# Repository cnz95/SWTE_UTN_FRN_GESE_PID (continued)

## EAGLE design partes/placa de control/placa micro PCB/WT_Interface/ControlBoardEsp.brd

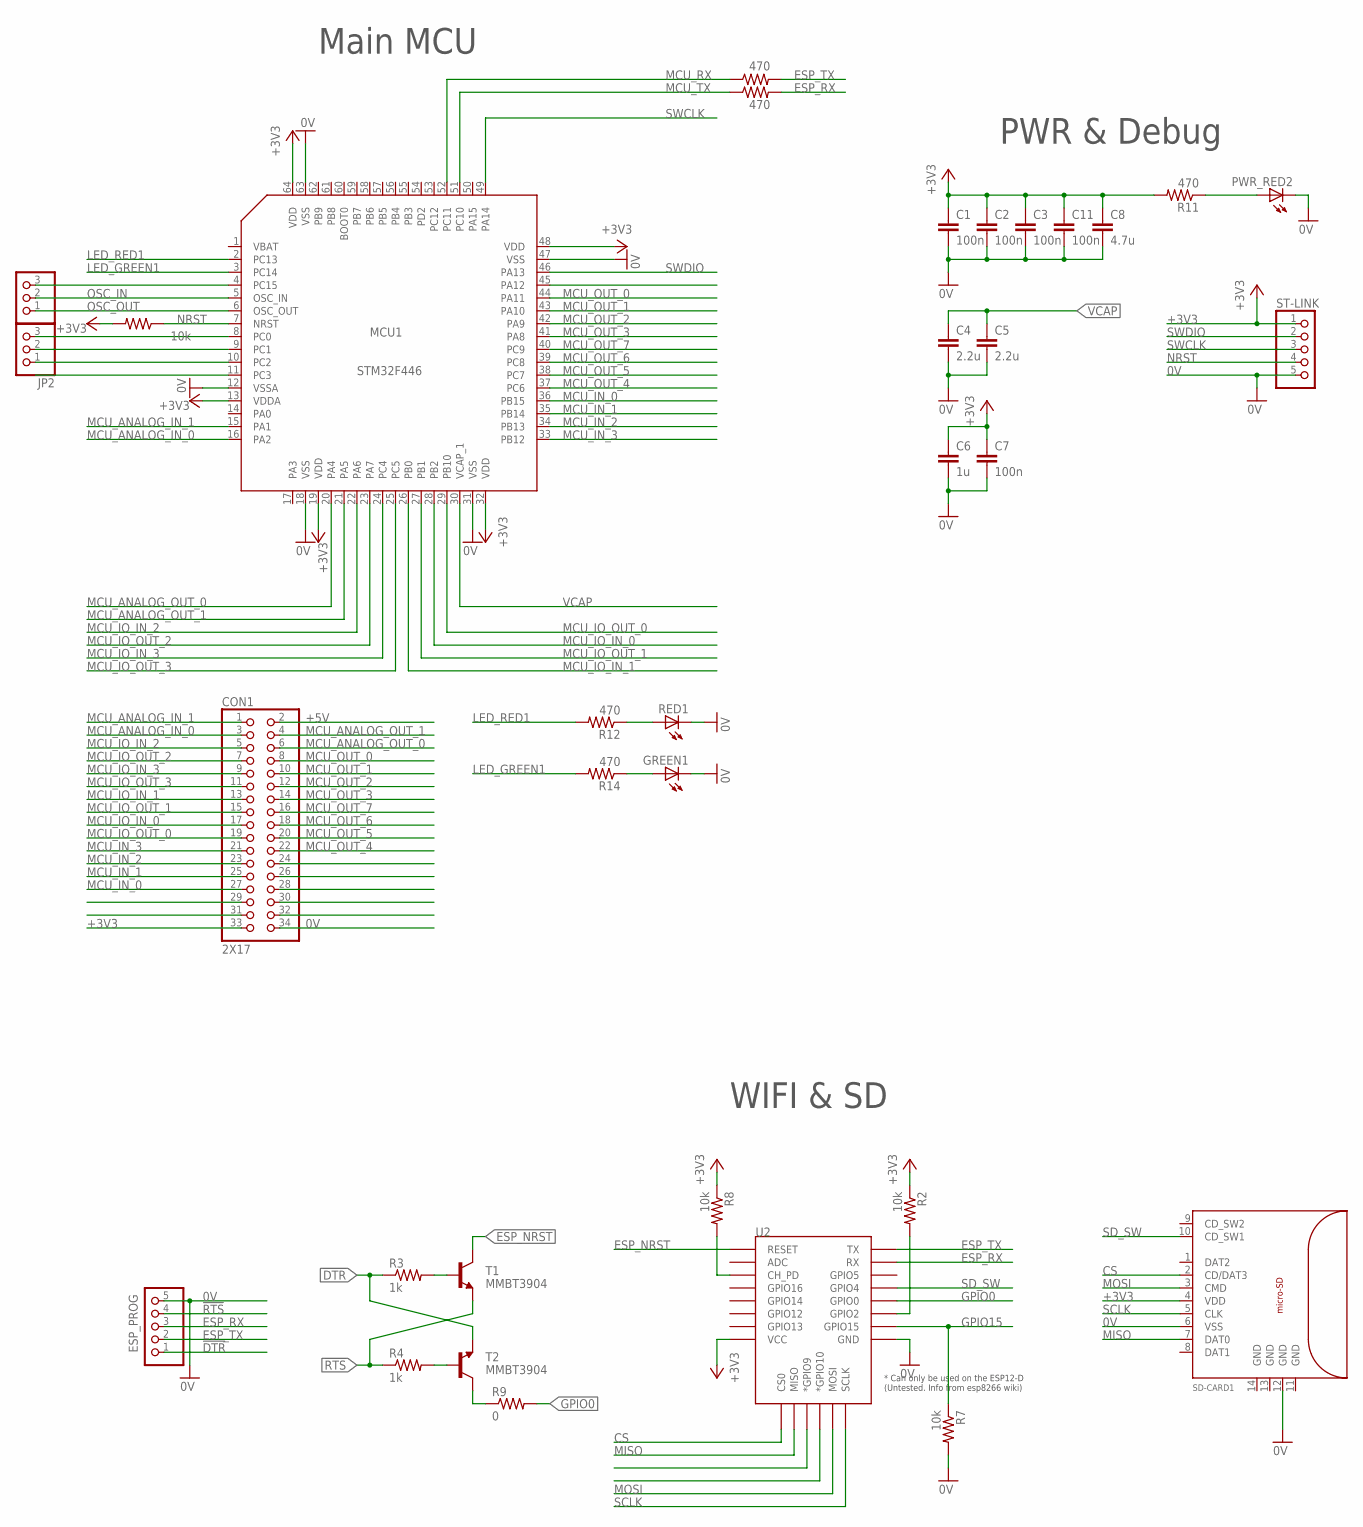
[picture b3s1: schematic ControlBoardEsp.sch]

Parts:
C1, C2, C3, C7, C11: 100n; C0402
C4, C5: 2.2u; C0402
C6: 1u; C0402
C8: 4.7u; C0402
CON1: 2X17
ESP_PROG: PINHD-1X5; 1X05
GREEN1: LEDCHIP-LED0805; CHIP-LED0805
JP1, JP2: PINHD-1X3; 1X03
MCU1: STM32F446; LQFP-64
PWR_RED2: LEDCHIP-LED0805; CHIP-LED0805
R1, R2, R7, R8: 10k; R0402
R3: 1k; R0402
R4: 1k; R1206
R5, R6, R11, R12, R14: 470; R0402
R9: 0; R1206
RED1: LEDCHIP-LED0805; CHIP-LED0805
SD-CARD1: MICRO-SD; MICRO_SD_FOOTPRINT
ST-LINK: PINHD-1X5; 1X05
T1, T2: MMBT3904; SOT23-BEC
U2: ESP12ESMD; ESP12E-SMD

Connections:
0V: C1.2, C2.2, C3.2, C4.2, C5.2, C6.2, C7.2, C8.2, C11.2, CON1.34, ESP_PROG.5, GREEN1.C, MCU1.12 (VSSA), MCU1.18 (VSS), MCU1.31 (VSS), MCU1.47 (VSS), MCU1.63 (VSS), PWR_RED2.C, R7.2, RED1.C, SD-CARD1.6 (VSS), SD-CARD1.12 (GND), ST-LINK.5, U2.GND
!DTR!: ESP_PROG.1, R3.1, T2.E
!RTS!: ESP_PROG.4, R4.1, T1.E
+3V3: C1.1, C2.1, C3.1, C6.1, C7.1, C8.1, C11.1, CON1.33, MCU1.13 (VDDA), MCU1.19 (VDD), MCU1.32 (VDD), MCU1.48 (VDD), MCU1.64 (VDD), R1.2, R2.1, R8.1, R11.2, SD-CARD1.4 (VDD), ST-LINK.1, U2.VCC
+5V: CON1.2
CS: SD-CARD1.2 (CD/DAT3), U2.CS0
ESP_NRST: T1.C, U2.RESET
ESP_RX: ESP_PROG.3, R6.2, U2.RXD0 (RX)
ESP_TX: ESP_PROG.2, R5.2, U2.TXD0 (TX)
GPIO0: R9.2, U2.GPIO0
GPIO15: R7.1, U2.GPIO15
LED_GREEN1: MCU1.3 (PC14), R14.2
LED_RED1: MCU1.2 (PC13), R12.2
MCU_ANALOG_IN_0: CON1.3, MCU1.16 (PA2)
MCU_ANALOG_IN_1: CON1.1, MCU1.15 (PA1)
MCU_ANALOG_OUT_0: CON1.6, MCU1.20 (PA4)
MCU_ANALOG_OUT_1: CON1.4, MCU1.21 (PA5)
MCU_IN_0: CON1.27, MCU1.36 (PB15)
MCU_IN_1: CON1.25, MCU1.35 (PB14)
MCU_IN_2: CON1.23, MCU1.34 (PB13)
MCU_IN_3: CON1.21, MCU1.33 (PB12)
MCU_IO_IN_0: CON1.17, MCU1.28 (PB2)
MCU_IO_IN_1: CON1.13, MCU1.26 (PB0)
MCU_IO_IN_2: CON1.5, MCU1.22 (PA6)
MCU_IO_IN_3: CON1.9, MCU1.24 (PC4)
MCU_IO_OUT_0: CON1.19, MCU1.29 (PB10)
MCU_IO_OUT_1: CON1.15, MCU1.27 (PB1)
MCU_IO_OUT_2: CON1.7, MCU1.23 (PA7)
MCU_IO_OUT_3: CON1.11, MCU1.25 (PC5)
MCU_OUT_0: CON1.8, MCU1.44 (PA11)
MCU_OUT_1: CON1.10, MCU1.43 (PA10)
MCU_OUT_2: CON1.12, MCU1.42 (PA9)
MCU_OUT_3: CON1.14, MCU1.41 (PA8)
MCU_OUT_4: CON1.22, MCU1.37 (PC6)
MCU_OUT_5: CON1.20, MCU1.38 (PC7)
MCU_OUT_6: CON1.18, MCU1.39 (PC8)
MCU_OUT_7: CON1.16, MCU1.40 (PC9)
MCU_RX: MCU1.52 (PC11), R5.1
MCU_TX: MCU1.51 (PC10), R6.1
MISO: SD-CARD1.7 (DAT0), U2.MISO
MOSI: SD-CARD1.3 (CMD), U2.MOSI
unnamed: R2.2, U2.GPIO2
unnamed: R3.2, T1.B
unnamed: R4.2, T2.B
unnamed: R8.2, U2.CH_PD
unnamed: R9.1, T2.C
unnamed: PWR_RED2.A, R11.1
unnamed: R12.1, RED1.A
unnamed: JP2.1, MCU1.10 (PC2)
unnamed: GREEN1.A, R14.1
unnamed: JP2.2, MCU1.9 (PC1)
unnamed: JP2.3, MCU1.8 (PC0)
unnamed: JP1.3, MCU1.4 (PC15)
NRST: MCU1.7 (NRST), R1.1, ST-LINK.4
OSC_IN: JP1.2, MCU1.5 (OSC_IN)
OSC_OUT: JP1.1, MCU1.6 (OSC_OUT)
SCLK: SD-CARD1.5 (CLK), U2.SCLK
SD_SW: SD-CARD1.10 (CD_SW1), U2.GPIO4
SWCLK: MCU1.49 (PA14), ST-LINK.3
SWDIO: MCU1.46 (PA13), ST-LINK.2
VCAP: C4.1, C5.1, MCU1.30 (VCAP_1)

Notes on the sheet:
PWR & Debug
Main MCU
WIFI & SD

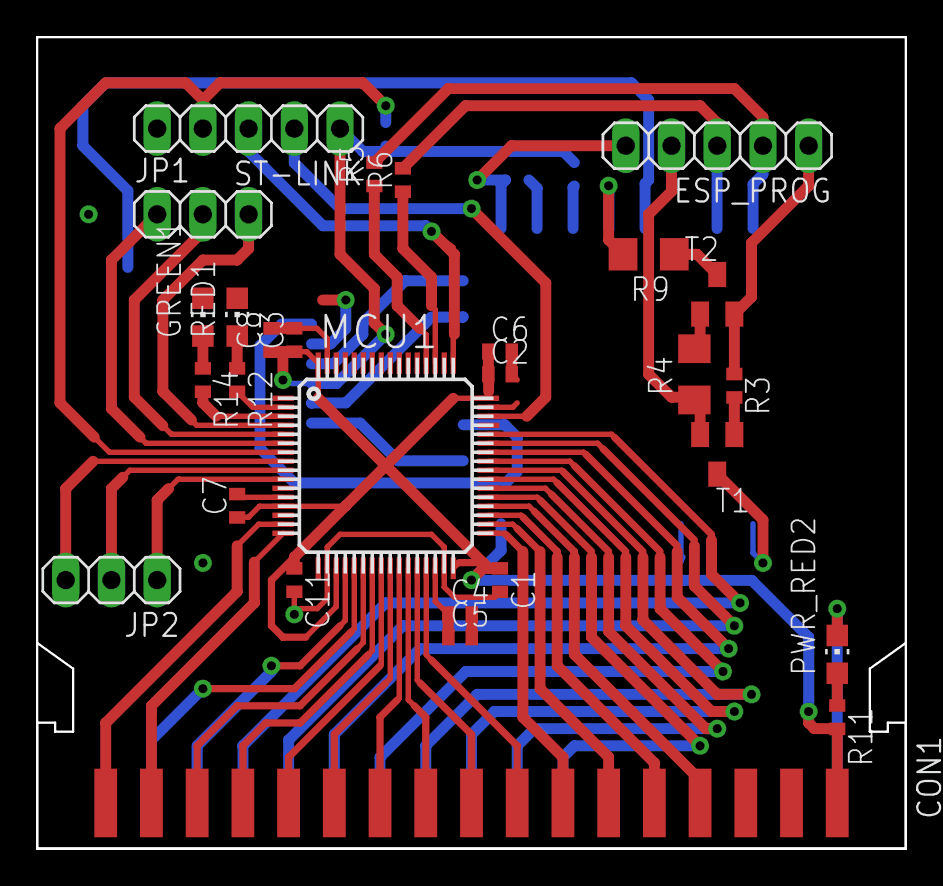
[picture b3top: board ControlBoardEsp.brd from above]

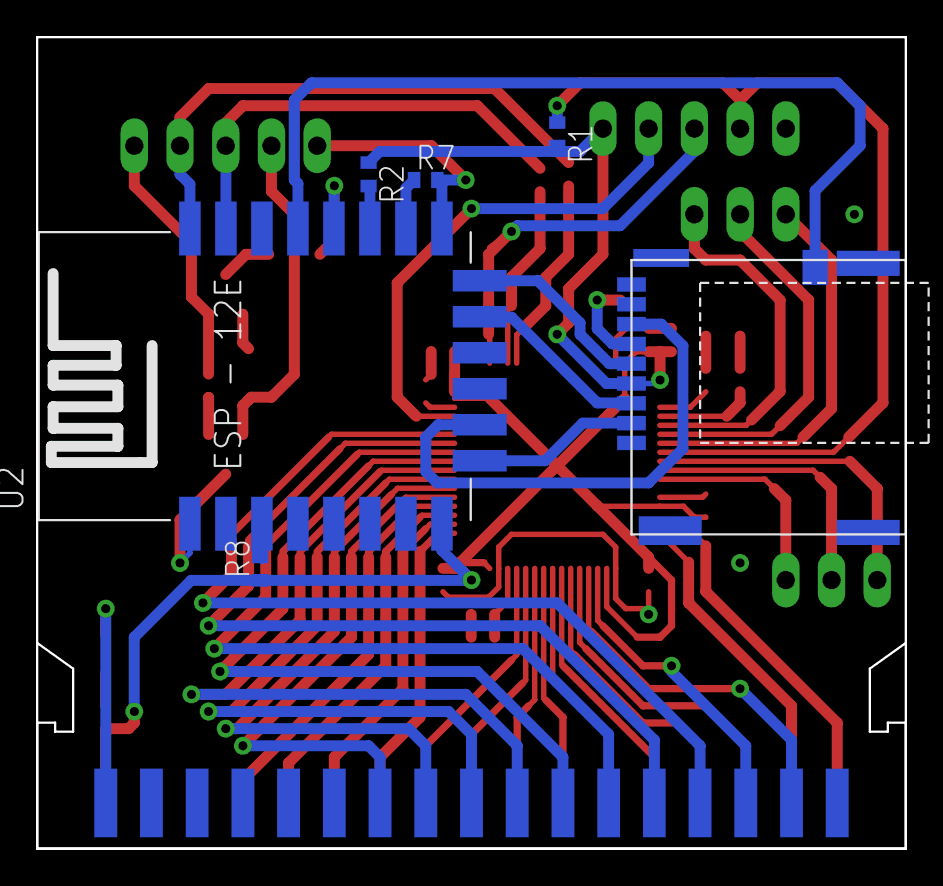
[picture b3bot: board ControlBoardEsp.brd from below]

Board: 2 copper layers, 48.3 x 45.1 mm, 34 parts (6 on the bottom side), 60 nets.

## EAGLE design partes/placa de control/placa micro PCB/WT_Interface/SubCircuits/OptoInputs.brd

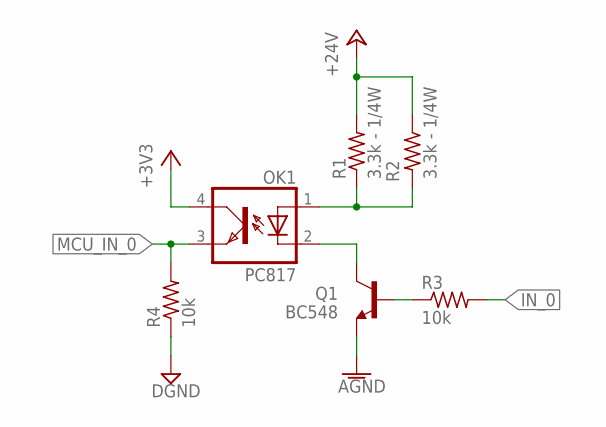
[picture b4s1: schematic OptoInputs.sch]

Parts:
OK1: PC817; DIL04
Q1: BC548; TO92-EBC
R1, R2: 3.3k - 1/4W; 0204V
R3: 10k; 0204/5
R4: 10k; R0402

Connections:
+3V3: OK1.4 (COL)
+24V: R1.2, R2.1
AGND: Q1.E
DGND: R4.1
IN_0: R3.2
MCU_IN_0: OK1.3 (EMIT), R4.2
unnamed: OK1.1 (A), R1.1, R2.2
unnamed: OK1.2 (C), Q1.C
unnamed: Q1.B, R3.1

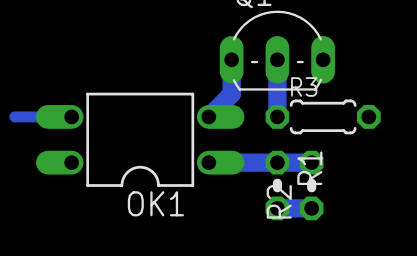
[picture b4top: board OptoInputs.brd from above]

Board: 2 copper layers, 6 parts (1 on the bottom side), 5 nets.

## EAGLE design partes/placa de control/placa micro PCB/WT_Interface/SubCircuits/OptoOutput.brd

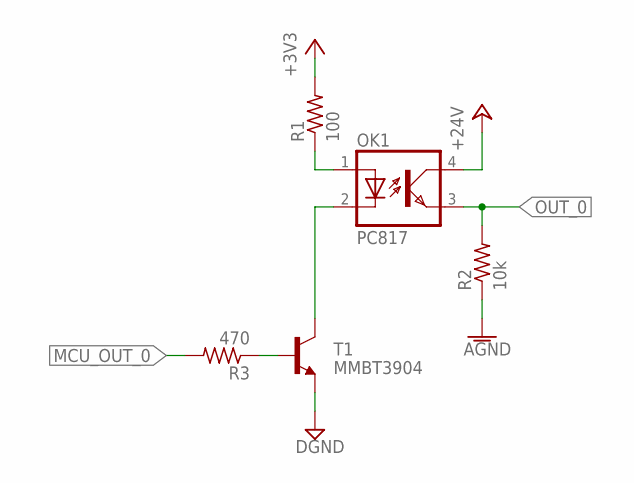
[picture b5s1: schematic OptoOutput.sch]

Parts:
OK1: PC817; DIL04
R1: 100; R0402
R2: 10k; R0402
R3: 470; 0204/5
T1: MMBT3904; SOT23-BEC

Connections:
+3V3: R1.2
+24V: OK1.4 (COL)
AGND: R2.1
DGND: T1.E
MCU_OUT_0: R3.2
unnamed: OK1.2 (C), T1.C
unnamed: R3.1, T1.B
unnamed: OK1.1 (A), R1.1
OUT_0: OK1.3 (EMIT), R2.2

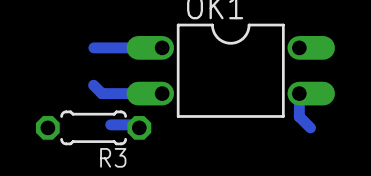
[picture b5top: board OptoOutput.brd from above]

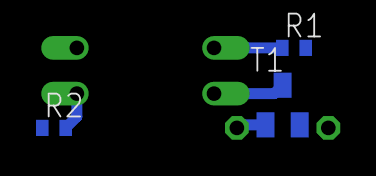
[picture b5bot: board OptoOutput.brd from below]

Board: 2 copper layers, 5 parts (3 on the bottom side), 4 nets.

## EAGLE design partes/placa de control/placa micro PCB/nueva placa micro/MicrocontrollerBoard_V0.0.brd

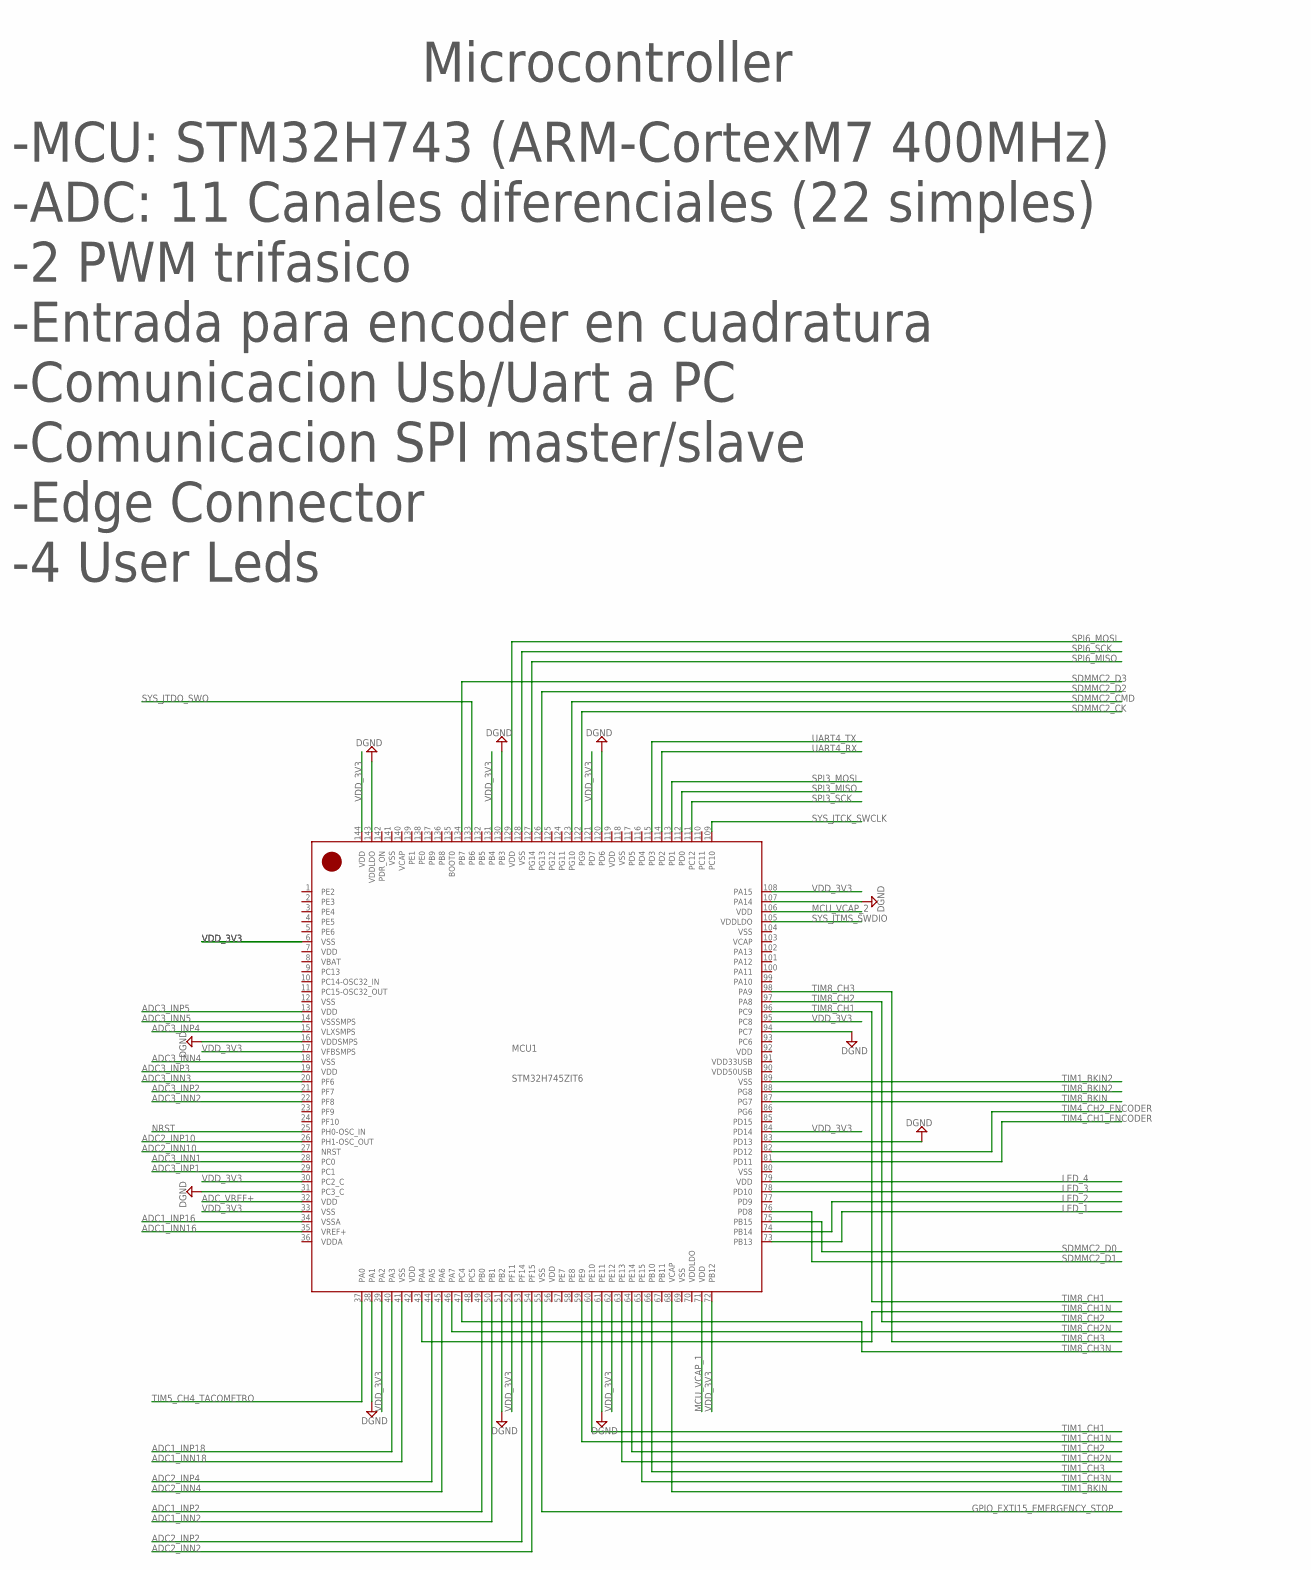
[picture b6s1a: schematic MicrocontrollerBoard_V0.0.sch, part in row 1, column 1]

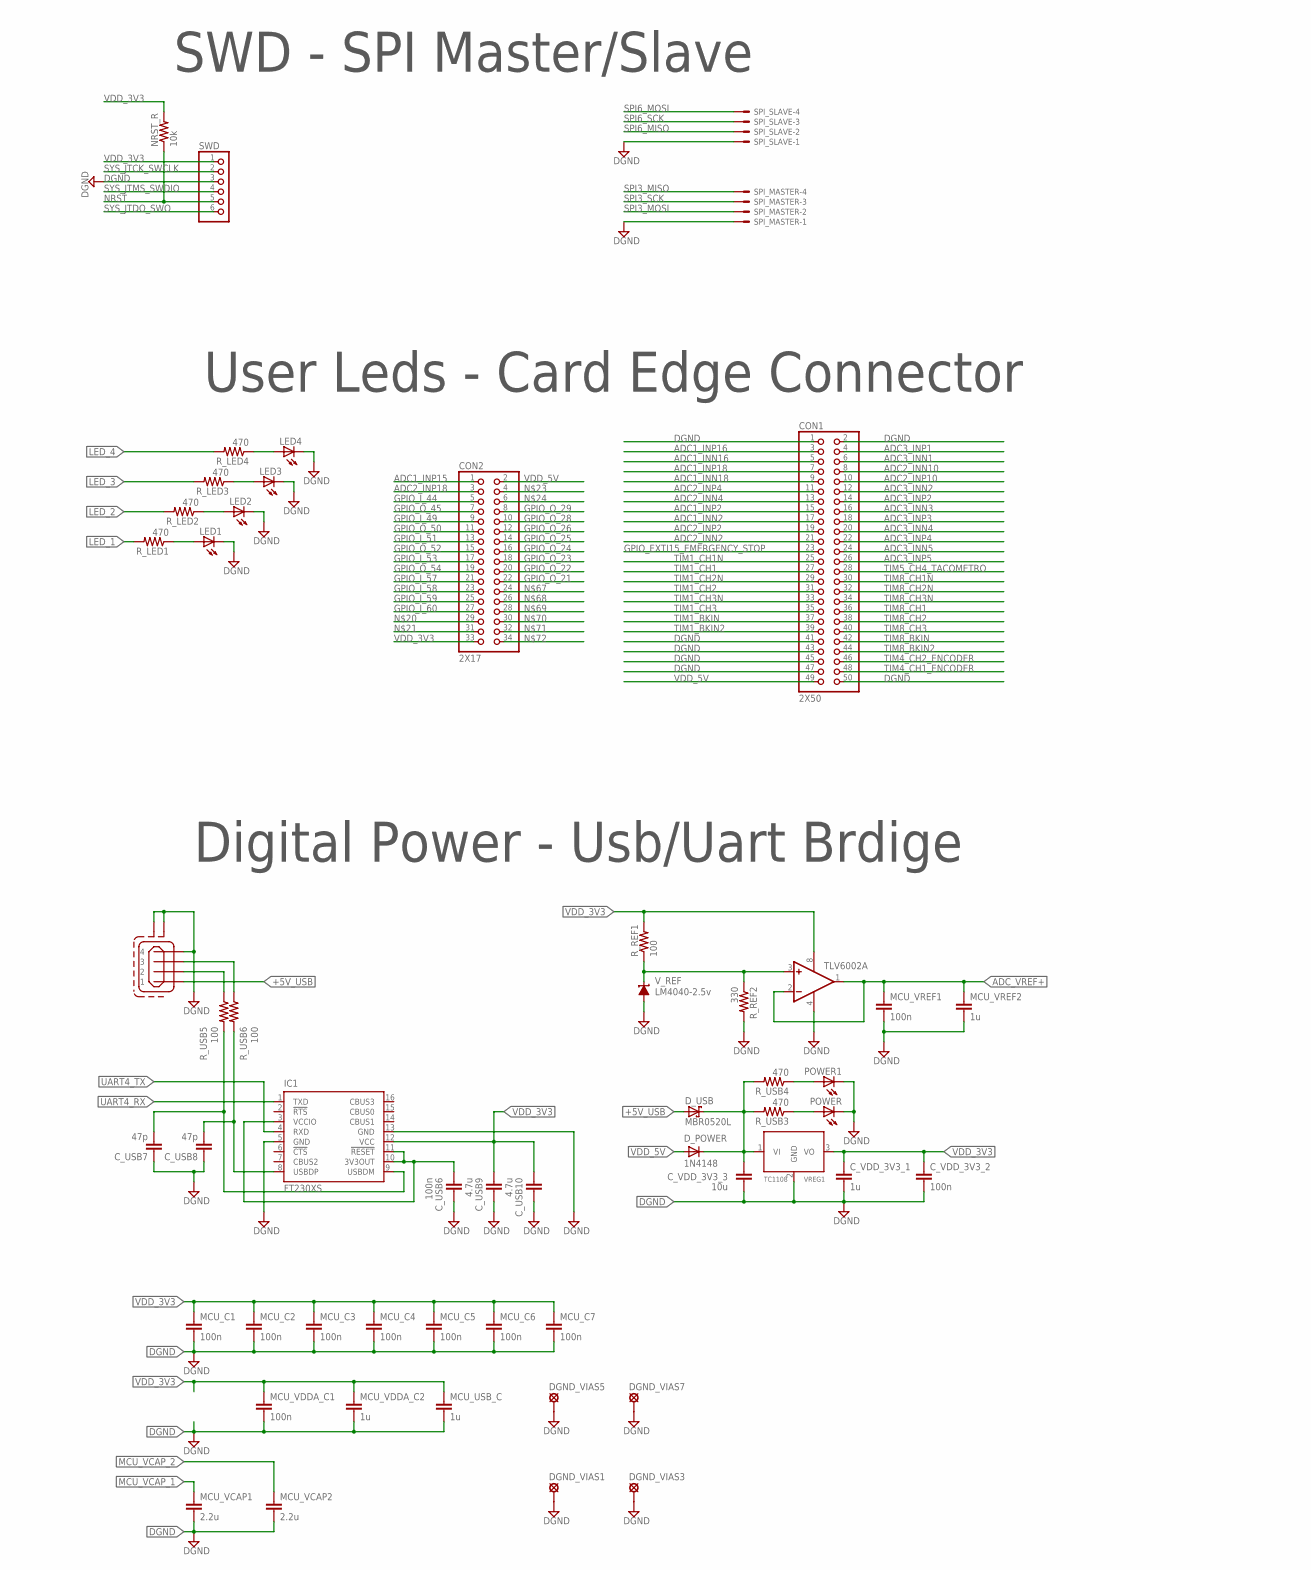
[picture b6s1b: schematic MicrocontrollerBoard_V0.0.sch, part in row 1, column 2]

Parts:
CON1: 2X50; 2X25
CON2: 2X17
C_USB6: 100n; C0402
C_USB7, C_USB8: 47p; C0402
C_USB9, C_USB10: 4.7u; C0402
C_VDD_3V3_1: 1u; C0603K
C_VDD_3V3_2: 100n; C0603K
C_VDD_3V3_3: 10u; C0603K
DGND_VIAS1, DGND_VIAS3, DGND_VIAS5, DGND_VIAS7: LSP10
D_POWER: 1N4148; SMA-DO214AC
D_USB: MBR0520L; SOD-123
IC1: FT230XS; SSOP16
LED1, LED2, LED3, LED4: LEDCHIPLED_0805; CHIPLED_0805
MCU1: STM32H745ZIT6144; LQFP144
MCU_C1, MCU_C2, MCU_C3, MCU_C4, MCU_C5, MCU_C6, MCU_C7: 100n; C0402
MCU_USB_C: 1u; C0402
MCU_VCAP1, MCU_VCAP2: 2.2u; C0402
MCU_VDDA_C1: 100n; C0402
MCU_VDDA_C2: 1u; C0402
MCU_VREF1: 100n; C0402
MCU_VREF2: 1u; C0402
NRST_R: 10k; R0402
POWER, POWER1: LEDCHIPLED_0805; CHIPLED_0805
R_LED1, R_LED2, R_LED3, R_LED4: 470; R0402
R_REF1: 100; R0805
R_REF2: 330; R0805
R_USB3, R_USB4: 470; R0402
R_USB5, R_USB6: 100; R0402
SPI_MASTER: 22-23-2041
SPI_SLAVE: 22-23-2041
SWD: PINHD-1X6/90; 1X06/90
TLV6002: TL082D; SO08
VREG1: TC1108'SOT-223'; SOT-223
V_REF: LM4040-2.5v; DBZ_R-PDSO-G3
X2: MINI-USB_SHIELD4P-85-32004-00X; 85-32004-00X

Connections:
+5V_USB: D_USB.A (IN), X2.1
ADC1_INN2: CON1.17, MCU1.50 (PB1)
ADC1_INN16: CON1.5, MCU1.35 (VREF+)
ADC1_INN18: CON1.9, MCU1.41 (VSS)
ADC1_INP2: CON1.15, MCU1.49 (PB0)
ADC1_INP15: CON2.1
ADC1_INP16: CON1.3, MCU1.34 (VSSA)
ADC1_INP18: CON1.7, MCU1.40 (PA3)
ADC2_INN2: CON1.21, MCU1.54 (PF15)
ADC2_INN4: CON1.13, MCU1.45 (PA6)
ADC2_INN10: CON1.8, MCU1.27 (NRST)
ADC2_INP2: CON1.19, MCU1.53 (PF14)
ADC2_INP4: CON1.11, MCU1.44 (PA5)
ADC2_INP10: CON1.10, MCU1.26 (PH1-OSC_OUT)
ADC2_INP18: CON2.3
ADC3_INN1: CON1.6, MCU1.28 (PC0)
ADC3_INN2: CON1.12, MCU1.22 (PF8)
ADC3_INN3: CON1.16, MCU1.20 (PF6)
ADC3_INN4: CON1.20, MCU1.18 (VSS)
ADC3_INN5: CON1.24, MCU1.14 (VSSSMPS)
ADC3_INP1: CON1.4, MCU1.29 (PC1)
ADC3_INP2: CON1.14, MCU1.21 (PF7)
ADC3_INP3: CON1.18, MCU1.19 (VDD)
ADC3_INP4: CON1.22, MCU1.15 (VLXSMPS)
ADC3_INP5: CON1.26, MCU1.13 (VDD)
ADC_VREF+: MCU1.32 (VDD), MCU_VREF1.1, MCU_VREF2.1, TLV6002.1 (OUT), TLV6002.2 (-IN)
DGND: CON1.1, CON1.2, CON1.41, CON1.43, CON1.45, CON1.47, CON1.50, C_USB6.1, C_USB7.1, C_USB8.1, C_USB9.1, C_USB10.1, C_VDD_3V3_1.2, C_VDD_3V3_2.2, C_VDD_3V3_3.2, DGND_VIAS1.MP, DGND_VIAS3.MP, DGND_VIAS5.MP, DGND_VIAS7.MP, IC1.5 (GND), IC1.13 (GND), LED1.C, LED2.C, LED3.C, LED4.C, MCU1.16 (VDDSMPS), MCU1.31 (PC3_C), MCU1.38 (PA1), MCU1.51 (PB2), MCU1.61 (PE11), MCU1.83 (PD13), MCU1.94 (PC7), MCU1.107 (PA14), MCU1.120 (PD6), MCU1.130 (PB3), MCU1.143 (VDDLDO), MCU_C1.2, MCU_C2.2, MCU_C3.2, MCU_C4.2, MCU_C5.2, MCU_C6.2, MCU_C7.2, MCU_USB_C.2, MCU_VCAP1.2, MCU_VCAP2.2, MCU_VDDA_C1.2, MCU_VDDA_C2.2, MCU_VREF1.2, MCU_VREF2.2, POWER.C, POWER1.C, R_REF2.2, SPI_MASTER.1, SPI_SLAVE.1, SWD.3, TLV6002.4 (V-), VREG1.2 (GND), V_REF.2 (A), X2.4, X2.M1 (S1), X2.M2 (S2)
GPIO_EXTI15_EMERGENCY_STOP: CON1.23, MCU1.55 (VSS)
GPIO_I_44: CON2.5
GPIO_I_49: CON2.9
GPIO_I_51: CON2.13
GPIO_I_53: CON2.17
GPIO_I_57: CON2.21
GPIO_I_58: CON2.23
GPIO_I_59: CON2.25
GPIO_I_60: CON2.27
GPIO_O_21: CON2.22
GPIO_O_22: CON2.20
GPIO_O_23: CON2.18
GPIO_O_24: CON2.16
GPIO_O_25: CON2.14
GPIO_O_26: CON2.12
GPIO_O_28: CON2.10
GPIO_O_29: CON2.8
GPIO_O_45: CON2.7
GPIO_O_50: CON2.11
GPIO_O_52: CON2.15
GPIO_O_54: CON2.19
LED_1: MCU1.73 (PB13), R_LED1.2
LED_2: MCU1.74 (PB14), R_LED2.2
LED_3: MCU1.78 (PD10), R_LED3.2
LED_4: MCU1.79 (VDD), R_LED4.2
MCU_VCAP_1: MCU1.71 (VDD), MCU_VCAP1.1
MCU_VCAP_2: MCU1.106 (VDD), MCU_VCAP2.1
unnamed: LED4.A, R_LED4.1
unnamed: POWER1.A, R_USB4.1
unnamed: LED3.A, R_LED3.1
unnamed: C_USB6.2, IC1.3 (VCCIO), IC1.10 (3V3OUT), IC1.11 (!RESET)
unnamed: C_VDD_3V3_3.1, D_POWER.K (C), D_USB.C (OUT), R_USB3.2, R_USB4.2, VREG1.1 (VI)
unnamed: C_USB8.2, IC1.8 (USBDP), R_USB6.2
unnamed: C_USB7.2, IC1.9 (USBDM), R_USB5.2
unnamed: R_USB5.1, X2.2
unnamed: R_USB6.1, X2.3
unnamed: POWER.A, R_USB3.1
unnamed: R_REF1.1, R_REF2.1, TLV6002.3 (+IN), V_REF.1 (C)
unnamed: LED1.A, R_LED1.1
unnamed: LED2.A, R_LED2.1
NRST: MCU1.25 (PH0-OSC_IN), NRST_R.1, SWD.5
SDMMC2_CK: MCU1.122 (PG9)
SDMMC2_CMD: MCU1.123 (PG10)
SDMMC2_D0: MCU1.75 (PB15)
SDMMC2_D1: MCU1.76 (PD8)
SDMMC2_D2: MCU1.126 (PG13)
SDMMC2_D3: MCU1.134 (PB7)
SPI3_MISO: MCU1.112 (PD0), SPI_MASTER.4
SPI3_MOSI: MCU1.113 (PD1), SPI_MASTER.2
SPI3_SCK: MCU1.111 (PC12), SPI_MASTER.3
SPI6_MISO: MCU1.127 (PG14), SPI_SLAVE.2
SPI6_MOSI: MCU1.129 (VDD), SPI_SLAVE.4
SPI6_SCK: MCU1.128 (VSS), SPI_SLAVE.3
SYS_JTCK_SWCLK: MCU1.109 (PC10), SWD.2
SYS_JTDO_SWO: MCU1.133 (PB6), SWD.6
SYS_JTMS_SWDIO: MCU1.105 (VDDLDO), SWD.4
TIM1_BKIN: CON1.37, MCU1.68 (VCAP)
TIM1_BKIN2: CON1.39, MCU1.89 (VSS)
TIM1_CH1: CON1.27, MCU1.60 (PE10)
TIM1_CH1N: CON1.25, MCU1.59 (PE9)
TIM1_CH2: CON1.31, MCU1.64 (PE14)
TIM1_CH2N: CON1.29, MCU1.63 (PE13)
TIM1_CH3: CON1.35, MCU1.66 (PB10)
TIM1_CH3N: CON1.33, MCU1.65 (PE15)
TIM4_CH1_ENCODER: CON1.48, MCU1.81 (PD11)
TIM4_CH2_ENCODER: CON1.46, MCU1.82 (PD12)
TIM5_CH4_TACOMETRO: CON1.28, MCU1.37 (PA0)
TIM8_BKIN: CON1.42, MCU1.87 (PG7)
TIM8_BKIN2: CON1.44, MCU1.88 (PG8)
TIM8_CH1: CON1.36, MCU1.96 (PC9)
TIM8_CH1N: CON1.30, MCU1.43 (PA4)
TIM8_CH2: CON1.38, MCU1.97 (PA8)
TIM8_CH2N: CON1.32, MCU1.46 (PA7)
TIM8_CH3: CON1.40, MCU1.98 (PA9)
TIM8_CH3N: CON1.34, MCU1.47 (PC4)
UART4_RX: IC1.1 (TXD), MCU1.114 (PD2)
UART4_TX: IC1.4 (RXD), MCU1.115 (PD3)
VDD_3V3: CON2.33, C_USB9.2, C_USB10.2, C_VDD_3V3_1.1, C_VDD_3V3_2.1, IC1.12 (VCC), MCU1.6 (VSS), MCU1.17 (VFBSMPS), MCU1.30 (PC2_C), MCU1.33 (VSS), MCU1.39 (PA2), MCU1.52 (PF11), MCU1.62 (PE12), MCU1.72 (PB12), MCU1.84 (PD14), MCU1.95 (PC8), MCU1.108 (PA15), MCU1.121 (PD7), MCU1.131 (PB4), MCU1.144 (VDD), MCU_C1.1, MCU_C2.1, MCU_C3.1, MCU_C4.1, MCU_C5.1, MCU_C6.1, MCU_C7.1, MCU_USB_C.1, MCU_VDDA_C1.1, MCU_VDDA_C2.1, NRST_R.2, R_REF1.2, SWD.1, TLV6002.8 (V+), VREG1.3 (VO)
VDD_5V: CON1.49, CON2.2, D_POWER.A

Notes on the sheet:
Microcontroller
SWD - SPI Master/Slave
User Leds - Card Edge Connector
Digital Power - Usb/Uart Brdige
-MCU: STM32H743 (ARM-CortexM7 400MHz) -ADC: 11 Canales diferenciales (22 simples) -2 PWM trifasico -Entrada para encoder en cuadratura -Comunicacion Usb/Uart a PC -Comunicacion SPI master/slave -Edge Connector -4 User Leds

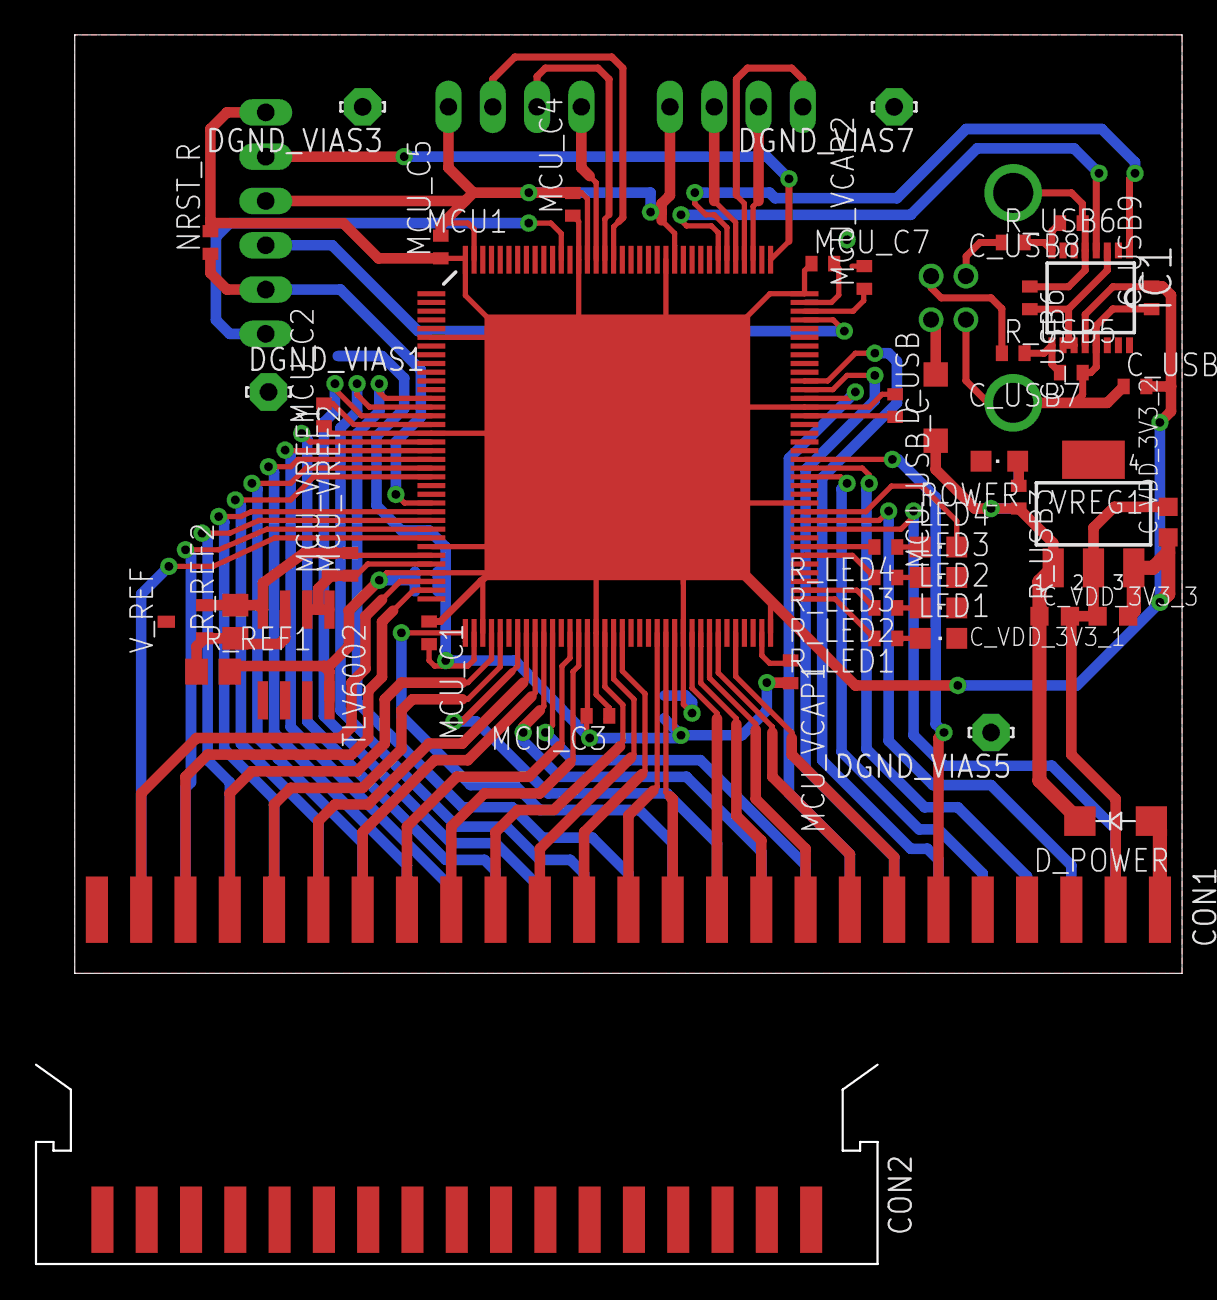
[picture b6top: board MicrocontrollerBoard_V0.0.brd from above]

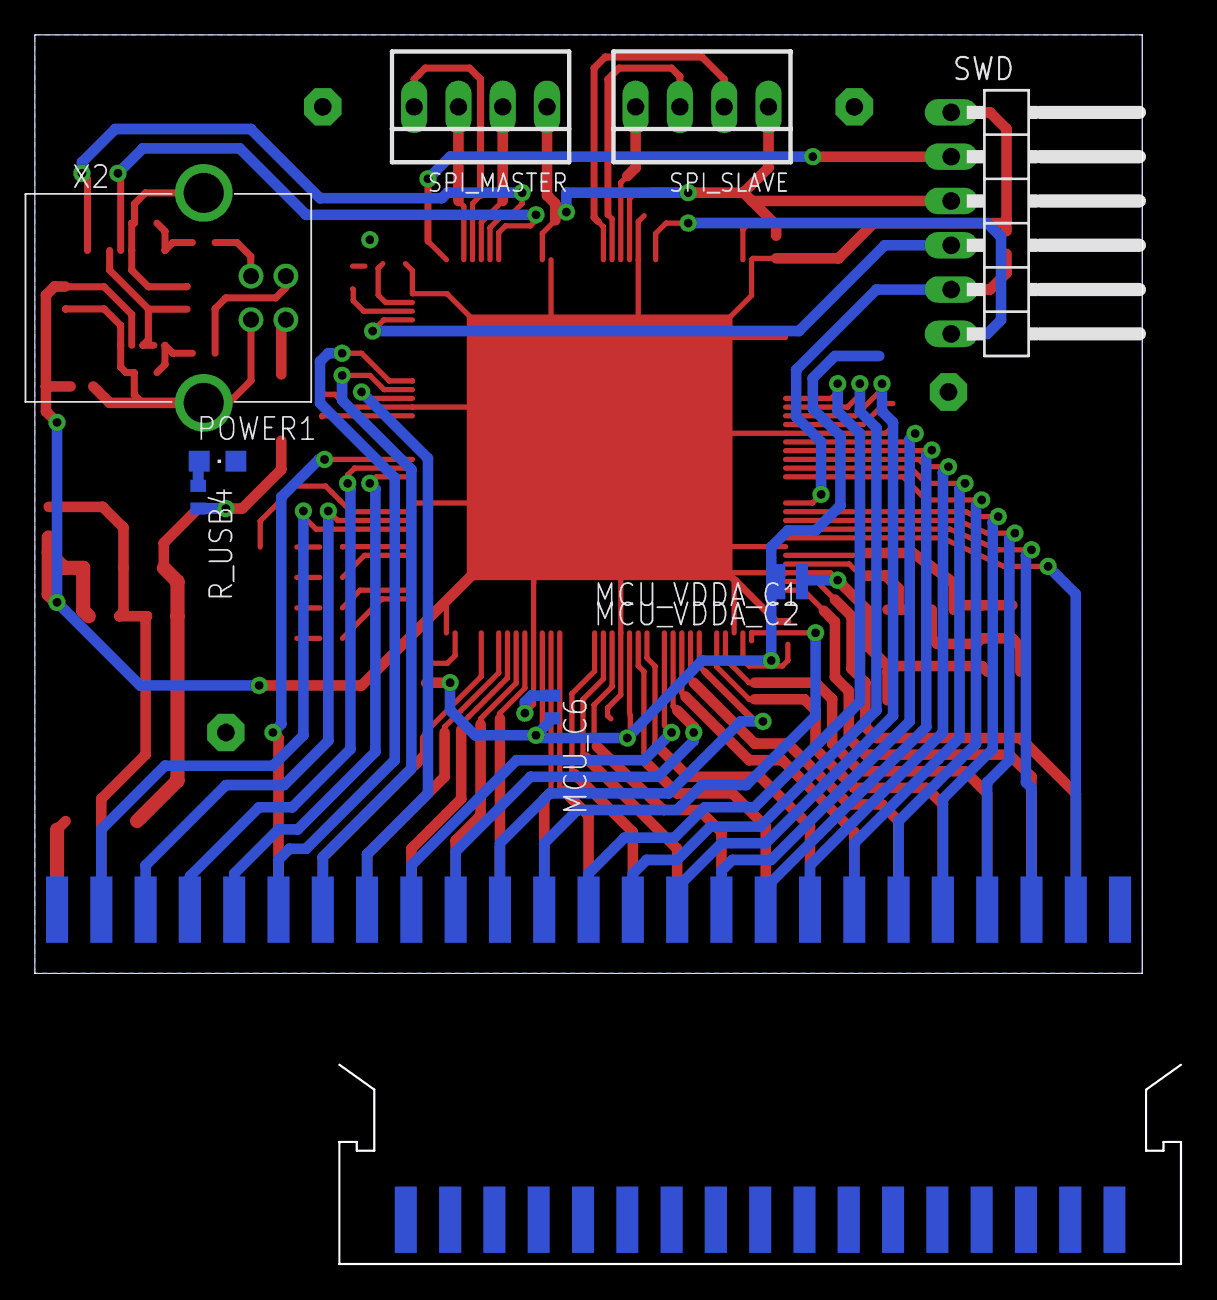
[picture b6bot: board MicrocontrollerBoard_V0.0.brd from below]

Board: 2 copper layers, 63.5 x 53.8 mm, 56 parts (9 on the bottom side), 78 nets.

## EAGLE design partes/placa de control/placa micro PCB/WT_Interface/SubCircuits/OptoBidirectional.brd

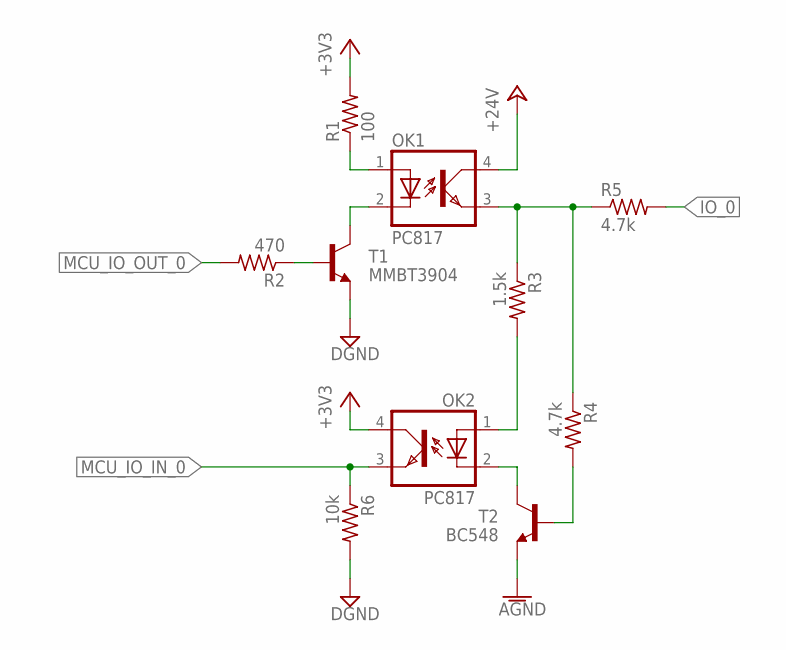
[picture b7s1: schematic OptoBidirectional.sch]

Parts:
OK1, OK2: PC817; DIL04
R1: 100; 0204/7
R2: 470; R0402
R3: 1.5k; 0204/5
R4, R5: 4.7k; 0204V
R6: 10k; 0204/5
T1: MMBT3904; SOT23-BEC
T2: BC548; TO92-CBE

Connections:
+3V3: OK2.4 (COL), R1.2
+24V: OK1.4 (COL)
AGND: T2.E
DGND: R6.2, T1.E
IO_0: R5.2
MCU_IO_IN_0: OK2.3 (EMIT), R6.1
MCU_IO_OUT_0: R2.2
unnamed: OK2.2 (C), T2.C
unnamed: OK1.2 (C), T1.C
unnamed: R2.1, T1.B
unnamed: OK1.1 (A), R1.1
unnamed: OK1.3 (EMIT), R3.1, R4.1, R5.1
unnamed: OK2.1 (A), R3.2
unnamed: R4.2, T2.B

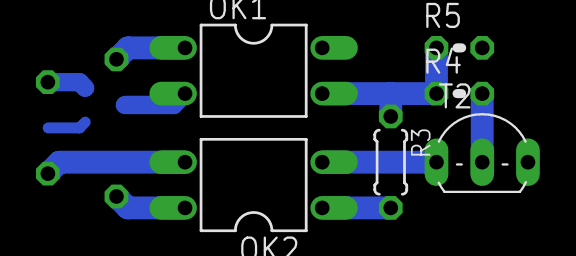
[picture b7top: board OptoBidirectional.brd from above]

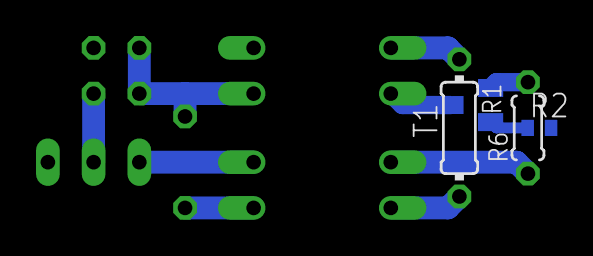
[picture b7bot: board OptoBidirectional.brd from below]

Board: 2 copper layers, 10 parts (4 on the bottom side), 10 nets.
